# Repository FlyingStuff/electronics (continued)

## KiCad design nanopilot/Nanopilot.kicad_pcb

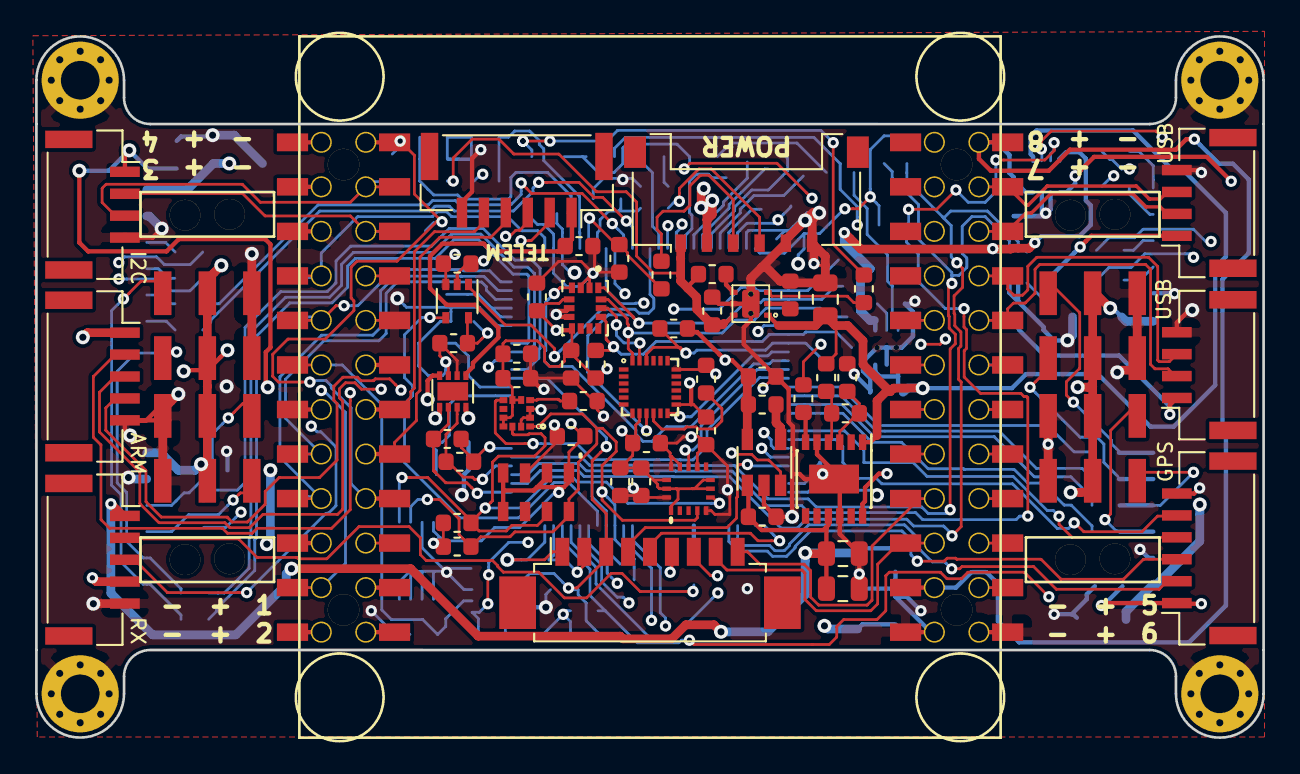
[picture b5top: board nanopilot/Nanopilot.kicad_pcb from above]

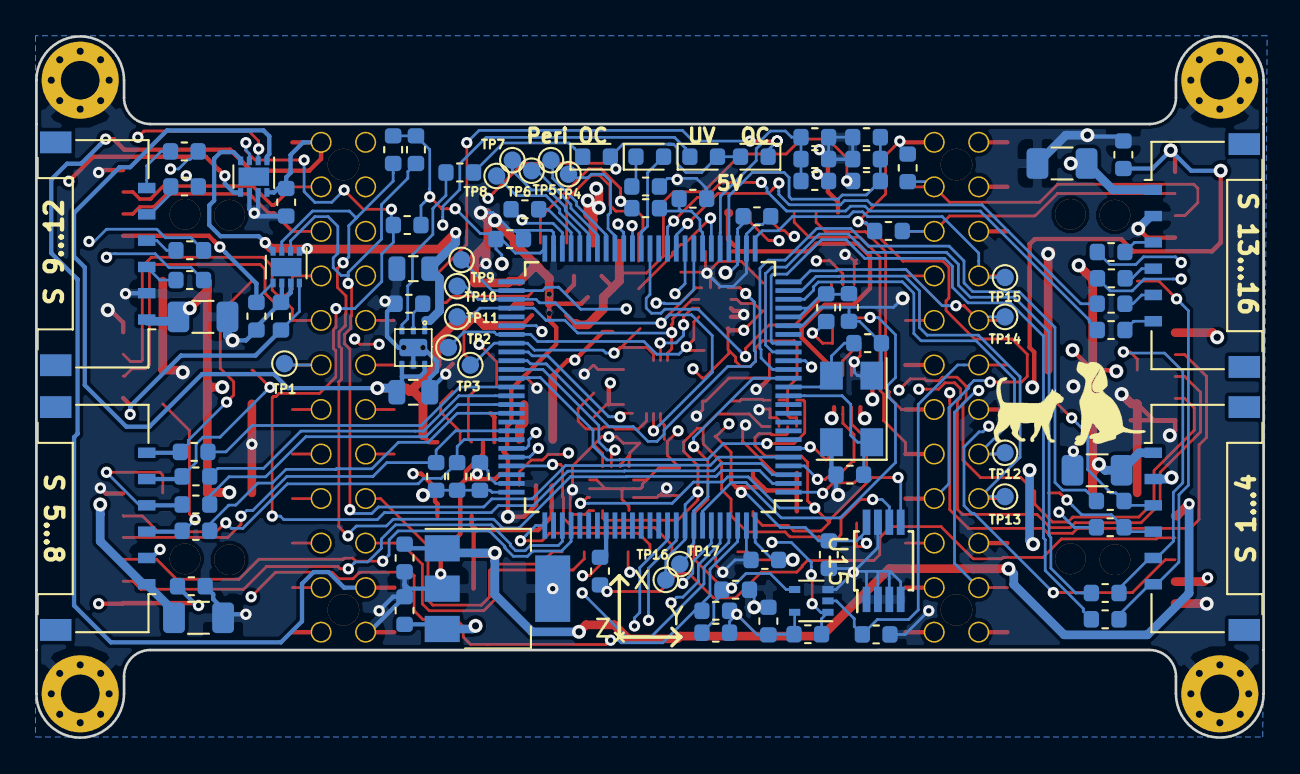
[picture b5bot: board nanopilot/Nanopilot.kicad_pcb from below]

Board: 4 copper layers, 70.0 x 40.0 mm, 161 parts (97 on the bottom side), 132 nets.

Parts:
C1, C3, C36: 10nF; C_0603_1608Metric
C2, C28, C29, C30, C31, C32, C33, C37, C40, C41, C45: 0.1uF; C_0603_1608Metric
C4, C5, C8, C15: 22uF; C_0805_2012Metric
C6, C39, C43, C44: 1uF; C_0603_1608Metric
C7, C12, C14, C42: 10uF; C_0603_1608Metric
C9: 100uF; C_0805_2012Metric
C10, C11: DNP; C_0603_1608Metric
C13: 0.01uF; C_0603_1608Metric
C16, C17: 22pF; C_0603_1608Metric
C18, C19, C20, C21, C22, C23, C34, C35, C38, C46, C47: 100nF; C_0603_1608Metric
C24, C25, C26, C27: 47uF; C_1206_3216Metric
D1: 5V UV; LED_0603_1608Metric
D2: OC 5V IN; LED_0603_1608Metric
D3: OC PERIPHERAL; LED_0603_1608Metric
D4: HEARTBEAT; LED_0603_1608Metric
J1: Conn_01x06; Molex_Pico-Lock_504050-0691_1x06-1MP_P1.50mm_Horizontal
J2: TELEM; JST_GH_SM06B-GHS-TB_1x06-1MP_P1.25mm_Horizontal
J3: GPS; JST_GH_SM06B-GHS-TB_1x06-1MP_P1.25mm_Horizontal
J4: USB1; JST_GH_SM04B-GHS-TB_1x04-1MP_P1.25mm_Horizontal
J5: USB2; JST_GH_SM04B-GHS-TB_1x04-1MP_P1.25mm_Horizontal
J6: I2C; JST_GH_SM04B-GHS-TB_1x04-1MP_P1.25mm_Horizontal
J7: ARM; JST_GH_SM05B-GHS-TB_1x05-1MP_P1.25mm_Horizontal
J8: DBG; Molex_PicoBlade_53261-0971_1x09-1MP_P1.25mm_Horizontal
J9: RX; JST_GH_SM05B-GHS-TB_1x05-1MP_P1.25mm_Horizontal
J10, J16: servo left; Molex_Pico-Lock_504050-0691_1x06-1MP_P1.50mm_Horizontal
J11, J17: servo right; Molex_Pico-Lock_504050-0691_1x06-1MP_P1.50mm_Horizontal
J12, J13: Servo Right; pin_headers_smd_2x03_P2.54mm_horizontal
J14, J15: Servo Left; pin_headers_smd_2x03_P2.54mm_horizontal
L1: L_Small; L_0603_1608Metric
MH1, MH2, MH3, MH4: MountingHole_Pad; MountingHole_2.2mm_M2_Pad_Via
R1: 812k; R_0603_1608Metric
R2: 247k; R_0603_1608Metric
R3, R5, R10, R20: 100k; R_0603_1608Metric
R4, R9: 220k; R_0603_1608Metric
R6, R7, R16, R17, R35, R36: 4.7k; R_0603_1608Metric
R8: 300k; R_0603_1608Metric
R11: 3.7k; R_0603_1608Metric
R12: 33k 1%; R_0603_1608Metric
R13, R19: 1.5k; R_0603_1608Metric
R14, R15: 0; R_0603_1608Metric
R18: 64k 1%; R_0603_1608Metric
R21, R22: 100; R_0603_1608Metric
R23: 1k; R_0603_1608Metric
R24, R25, R26, R27, R28, R29, R30, R31, R32, R33, R34: 10k; R_0603_1608Metric
R37, R38, R39, R40, R41, R42, R43, R44, R45, R46, R47, R48, R49, R50, R51, R52: 200; R_0603_1608Metric
TP1: Time; TestPoint_Pad_D1.0mm
TP2: CS_LSM; TestPoint_Pad_D1.0mm
TP3: CS_MPU; TestPoint_Pad_D1.0mm
TP4, TP5, TP6, TP7, TP8: TestPoint; TestPoint_Pad_D1.0mm
TP9, TP16: SCL; TestPoint_Pad_D1.0mm
TP10: MISO; TestPoint_Pad_D1.0mm
TP11: MOSI; TestPoint_Pad_D1.0mm
TP12: CTS; TestPoint_Pad_D1.0mm
TP13: RTS; TestPoint_Pad_D1.0mm
TP14: TX; TestPoint_Pad_D1.0mm
TP15: RX; TestPoint_Pad_D1.0mm
TP17: SDA; TestPoint_Pad_D1.0mm
U1: LTC4419; MSOP-12-1EP_3x4mm_P0.65mm_EP1.65x2.85mm
U2: NanoPi_Air_1.1; NanoPi_Header
U3, U6: TPS25200; TPS25200_WSON_6
U4: LT1963EST-3.3; SOT-223
U5: LT1761-3.3; TSOT-23-5
U7: STM32F303VETx; LQFP-100_14x14mm_P0.5mm
U8, U9, U10: SiP32414; DFN-8-1EP_2x2mm_P0.5mm_EP1.05x1.75mm
U11: SN74LVC1G08; SOT-353_SC-70-5
U12: SN74LVC1G38; SOT-353_SC-70-5
U13: LSM6DSM; PQFN50P300X250X86-14N
U14: MPU-9250; MPU-9250_QFN-24_0.4mm
U15: 24LC256; MSOP-8_3x3mm_P0.65mm
U16: MS5611-01BA03; MS5611-01BA
U17: LIS3MDL; LGA12R50P4X4_200X200X100
U18: VAL**; H3LIS331DL
Y1: 8MHz; Crystal_SMD_Abracon_ABM3C-4Pin_5.0x3.2mm

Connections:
+3V3: C12.1, C19.1, C20.1, C21.1, C22.1, C34.1, C35.1, J8.1, J9.4, L1.1, R6.1, R7.1, R20.1, R24.1, R25.1, R26.1, R27.1, R28.1, R29.1, R30.1, U4.3, U7.6, U7.28, U7.50, U7.75, U7.100, U11.5, U12.5
+3V3_NANOPI: R16.1, R17.1, U2.B1, U2.B17
+5V: C8.1, C9.1, R1.1, U1.1, U3.1, U6.4, U6.6, U8.1
+5V_NANOPI: C31.2, U2.A1, U2.A22, U2.B2, U2.B4, U8.8
/3V3_SENS: C13.1, C14.1, C36.1, C37.1, C38.1, C39.1, C40.1, C42.1, C43.1, C44.1, C45.1, C46.1, R33.1, R34.1, R35.1, R36.1, U5.5, U13.5, U13.8, U14.8, U14.13, U15.8, U16.1, U16.2, U16.4, U16.5, U17.5, U17.6, U17.9, U17.10, U18.1, U18.7, U18.8, U18.14, U18.15
/5V_IN_ADC: C3.1, R9.2, R10.1, U7.29
/5V_in: C2.1, J1.1, R8.2, R9.1, U3.6
/ARM_LED: J7.2, U7.40
/ARM_SWITCH: J7.3, U7.41
/BOOT: U7.94, U11.4
/GPS_I2C_SCL: J3.4, R7.2, U7.68
/GPS_I2C_SDA: J3.5, R6.2, U7.69
/GPS_POWER: C28.2, J3.1, U8.5
/GPS_POWER_EN: R24.2, U7.3, U8.3
/GPS_RX: J3.3, U7.79
/GPS_TX: J3.2, U7.78
/H3LIS_INT: U7.61, U18.11
/HEARTBEAT_LED: D4.2, U7.39
/I2C_POWER: C29.2, J6.1, U10.8
/I2C_POWER_EN: R26.2, U7.1, U10.2
/I2C_SENS_SCL: R36.2, TP16.1, U7.92, U15.6, U16.8, U17.1, U18.4
/I2C_SENS_SDA: R35.2, TP17.1, U7.93, U15.5, U16.7, U17.11, U18.6
/I_bat_adc: C10.1, R14.2, U7.31
/I_bat_sens: J1.3, R14.1
/LIS3MDL_INT: U7.62, U17.7
/LL_CTRL_POWER: C4.1, C5.1, C6.1, C7.1, D1.2, D2.2, D3.2, J9.1, U1.9, U4.1, U5.1
/LSM_INT1: U7.60, U13.4
/MPU_INT: U7.59, U14.12
/NANOPI_I2C_SCL: J6.2, R17.2, U2.B5
/NANOPI_I2C_SDA: J6.3, R16.2, U2.B3
/NANOPI_POWER_EN: R27.2, U7.98, U8.2
/NPI_DBG_RX: J8.9, U2.A18
/NPI_DBG_TX: J8.8, U2.A20
/NRST: C18.1, J8.3, R20.2, U7.14, U12.4
/RC_IN: J9.2, R21.1
/RESET_CTRL_EN: R30.2, U7.38, U11.1, U12.1
/RSSI/TELEM: J9.3, R22.2, U7.48
/SERVO1_PWM: J14.1, J16.3, R45.1
/SERVO2_PWM: J14.2, J16.4, R46.1
/SERVO3_PWM: J15.1, J16.5, R47.1
/SERVO4_PWM: J15.2, J16.6, R48.1
/SERVO5_PWM: J12.1, J17.3, R52.1
/SERVO6_PWM: J12.2, J17.4, R51.1
/SERVO7_PWM: J13.1, J17.5, R50.1
/SERVO8_PWM: J13.2, J17.6, R49.1
/SERVO9_PWM: J10.3, R37.1
/SERVO10_PWM: J10.4, R38.1
/SERVO11_PWM: J10.5, R43.1
/SERVO12_PWM: J10.6, R44.1
/SERVO13_PWM: J11.3, R41.1
/SERVO14_PWM: J11.4, R42.1
/SERVO15_PWM: J11.5, R39.1
/SERVO16_PWM: J11.6, R40.1
/SPEAKER: J7.4, U2.A10
/SPI_SENS_MISO: TP10.1, U7.53, U13.1, U14.9
/SPI_SENS_MOSI: TP11.1, U7.54, U13.14, U14.24
/SPI_SENS_SCLK: TP9.1, U7.52, U13.13, U14.23
/STM_CTRL_BOOTLOADER: R31.1, U2.B7, U11.2
/STM_CTRL_RESET: R32.1, U2.B12, U12.2
/STM_DBG_RX: J8.7, U7.34
/STM_DBG_TX: J8.6, U7.33
/SWCLK: J8.5, U7.76
/SWDIO: J8.4, U7.72
/TELEM_CTS: J2.4, U2.B15
/TELEM_POWER: C32.2, J2.1, U10.5
/TELEM_POWER_EN: R29.2, U7.4, U10.3
/TELEM_RTS: J2.5, U2.B13
/TELEM_RX: J2.3, U2.B22
/TELEM_TX: J2.2, U2.B11
/TIME_SYNC: TP1.1, U2.A11, U7.56
/USART2_CTS: TP12.1, U2.B16, U7.23
/USART2_RTS: TP13.1, U2.B18, U7.24
/USART2_RX: TP15.1, U2.B8, U7.26
/USART2_TX: TP14.1, U2.B10, U7.25
/USB2_D+: J4.3, U2.A3
/USB2_D-: J4.2, U2.A5
/USB2_POWER: C30.2, J4.1, U9.5
/USB2_POWER_EN: R25.2, U7.2, U9.3
/USB3_D+: J5.3, U2.A7
/USB3_D-: J5.2, U2.A9
/USB3_POWER: C33.2, J5.1, U9.8
/USB3_POWER_EN: R28.2, U7.5, U9.2
/V_SERVO: C24.1, C25.1, C26.1, C27.1, J1.2, J10.1, J11.1, J12.3, J12.4, J13.3, J13.4, J14.3, J14.4, J15.3, J15.4, J16.1, J17.1, R4.1, U1.12
/V_SERVO_ADC: C1.1, R4.2, R5.1, U7.30
/V_bat_adc: C11.1, R15.2, U7.32
/V_bat_sens: J1.4, R15.1
/V_peripheral: C15.1, J7.1, U6.1, U8.4, U9.1, U9.4, U10.1, U10.4
/~LSM_CS: R33.2, TP2.1, U7.57, U13.12
/~MPU_CS: R34.2, TP3.1, U7.58, U14.22
/~SHDN_SENS: U5.3, U7.97
GND: C1.2, C2.2, C3.2, C4.2, C5.2, C6.2, C7.2, C8.2, C9.2, C10.2, C11.2, C12.2, C14.2, C15.2, C16.2, C17.2, C18.2, C19.2, C20.2, C21.2, C22.2, C23.2, C24.2, C25.2, C26.2, C27.2, C28.1, C29.1, C30.1, C31.1, C32.1, C33.1, C34.2, C35.2, C36.2, C37.2, C38.2, C39.2, C40.2, C41.2, C42.2, C43.2, C44.2, C45.2, C46.2, C47.2, J1.5, J1.6, J2.6, J3.6, J4.4, J5.4, J6.4, J7.5, J8.2, J9.5, J10.2, J11.2, J12.5, J12.6, J13.5, J13.6, J14.5, J14.6, J15.5, J15.6, J16.2, J17.2, MH1.1, MH2.1, MH3.1, MH4.1, R3.2, R5.2, R10.2, R12.2, R18.2, R23.2, R31.2, R32.2, U1.5, U1.10, U1.13, U2.A23, U2.A24, U2.B6, U2.B9, U2.B14, U2.B20, U3.5, U3.7, U4.2, U4.4, U5.2, U6.5, U6.7, U7.20, U7.27, U7.49, U7.74, U7.99, U8.6, U8.7, U9.6, U9.7, U10.6, U10.7, U11.3, U12.3, U13.2, U13.3, U13.6, U13.7, U14.18, U15.1, U15.2, U15.3, U15.4, U15.7, U16.3, U17.2, U17.3, U17.12, U18.5, U18.10, U18.12, U18.13, U18.16, Y1.2, Y1.4
unnamed: C13.2, U5.4
unnamed: C16.1, U7.12, Y1.1
unnamed: C17.1, U7.13, Y1.3
unnamed: C41.1, U14.10
unnamed: C47.1, U17.4
unnamed: D1.1, R11.1
unnamed: D2.1, R13.1
unnamed: D3.1, R19.1
unnamed: D4.1, R23.1
unnamed: R1.2, R2.1, U1.4
unnamed: R2.2, R3.1, U1.3
unnamed: R8.1, U3.4
unnamed: R11.2, U1.6
unnamed: R12.1, U3.2
unnamed: R13.2, U3.3
unnamed: R18.1, U6.2
unnamed: R19.2, U6.3
unnamed: R21.2, U7.83
unnamed: R22.1, U7.47
unnamed: R37.2, U7.70
unnamed: R38.2, U7.71
unnamed: R39.2, U7.35
unnamed: R40.2, U7.36
unnamed: R41.2, U7.90
unnamed: R42.2, U7.91
unnamed: R43.2, U7.95
unnamed: R44.2, U7.96
unnamed: R45.2, U7.15
unnamed: R46.2, U7.16
unnamed: R47.2, U7.17
unnamed: R48.2, U7.18
unnamed: R49.2, U7.63
unnamed: R50.2, U7.64
unnamed: R51.2, U7.65
unnamed: R52.2, U7.66
unnamed: TP4.1, U7.42
unnamed: TP5.1, U7.43
unnamed: TP6.1, U7.44
unnamed: TP7.1, U7.45
unnamed: TP8.1, U7.46
VDDA: C23.1, L1.2, U7.21, U7.22

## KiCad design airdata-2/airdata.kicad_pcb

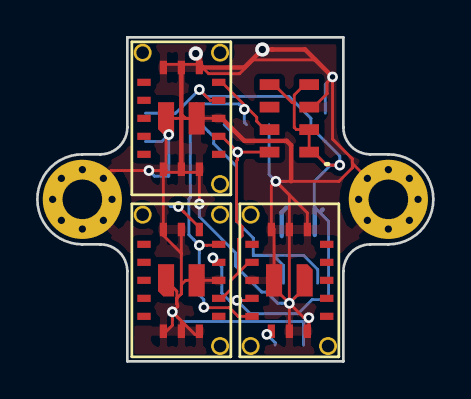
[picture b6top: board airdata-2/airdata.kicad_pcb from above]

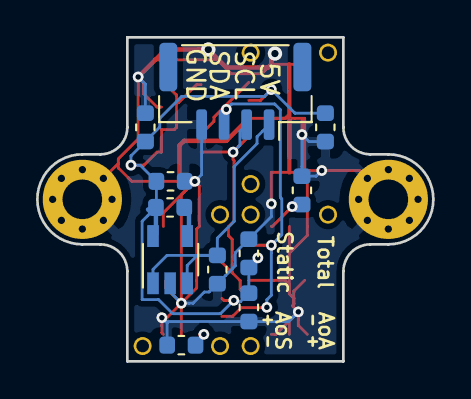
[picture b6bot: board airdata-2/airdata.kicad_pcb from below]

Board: 2 copper layers, 22.0 x 18.0 mm, 17 parts (11 on the bottom side), 8 nets.

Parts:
C1, C2, C3, C7: 100nF; C_0603_1608Metric
C4: 1uF; C_0603_1608Metric
C6: 0.01uF; C_0603_1608Metric
C8: 10uF; C_0603_1608Metric
J1: I2C; JST_GH_SM04B-GHS-TB_1x04-1MP_P1.25mm_Horizontal
MH1, MH2: MountingHole_Pad; MountingHole_2.2mm_M2_Pad_Via
R2: 1.2k; R_0603_1608Metric
R3: 2.7k; R_0603_1608Metric
U1, U3, U6: SDP33; SDP3x
U2: MS5611-01BA03; MS5611-01BA
U4: LT1761-3.3; TSOT-23-5

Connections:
+3V3: C1.1, C2.1, C3.1, C6.1, C7.1, C8.1, U1.7, U2.1, U2.2, U2.4, U2.5, U3.7, U4.5, U6.7
+5V: C4.1, J1.1, U4.1, U4.3
/SCL: J1.2, U1.5, U2.8, U3.5, U6.5
/SDA: J1.3, U1.8, U2.7, U3.8, U6.8
GND: C1.2, C2.2, C3.2, C4.2, C7.2, C8.2, J1.4, MH1.1, MH2.1, R2.2, R3.2, U1.1, U1.2, U1.3, U1.6, U1.9, U1.10, U1.11, U2.3, U3.1, U3.2, U3.3, U3.6, U3.10, U3.11, U4.2, U6.1, U6.2, U6.3, U6.6, U6.10, U6.11
unnamed: C6.2, U4.4
unnamed: R2.1, U3.9
unnamed: R3.1, U6.9

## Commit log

2018-09-08 nanopilot schematics and pcb
2018-09-09 sensors library
2018-09-11 finalize pin assingment & pullup/down
2018-09-11 move to subdirectory
2018-09-19 schematic
2018-10-04 nanopi footprints and schematics footprints
2018-10-04 symbols
2018-10-04 clean up libraries
2018-10-04 airdata board
2018-10-04 power supply board
2018-10-04 airdata footprints & 3d models
2018-10-10 airdata & power supply pcb
2018-10-24 version ready to be routed
2018-10-24 power board remove silkscreen & add usb 3d model
2018-10-24 hide references on silkscreen
2018-10-29 routing nanopilot WIP
2018-10-31 routing WIP
2018-11-09 last review before fabrication
2018-11-10 nanopilot fabrication final version
2018-11-10 power supply and airspeed sensor for fabrication
2018-11-10 change capacitors
2019-05-12 nanopilot duo with pressure sensors
2019-05-27 finished routing
2019-05-27 silkscreen & gerber
2019-05-27 schematic pdf
2019-06-18 Nanopilot Duo: final BOM and some component value changes
2019-06-18 new airdata board
2019-06-19 differential i2c driver
2020-03-10 power supply notes
2020-03-10 rename nanopilot to nanopilot air
